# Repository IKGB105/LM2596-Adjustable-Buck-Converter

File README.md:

# Adjustable Buck Converter (LM2596)

Adjustable step-down (buck) power supply based on the LM2596S-ADJ, documented as an honest engineering
logbook: every result is marked as calculated, simulated, or pending — no invented placeholders. A quick,
deliberately simple project in the same series as
[LM317-Adjustable-PowerSupply](https://github.com/IKGB105/LM317-Adjustable-PowerSupply) (same thermal
analysis style, meant as a direct comparison point) — built mainly to get hands-on KiCad PCB layout
experience (placement, trace widths, a ground-plane strategy, via stitching) before moving on to
multiphase VRM work.

- **Input:** 12–40 V DC (datasheet reference design)
- **Adjustable output:** 1.23 V to ≈ 35 V (RV1 position-dependent, see report)
- **Demonstration condition used for thermal comparison:** 12 V → 2 V @ 0.5 A (same load as the LM317
  companion project)

> ⚠️ **Not safe across the full adjustable range.** At the low-output-voltage extreme (35 V → 1.23 V),
> the catch diode D1 exceeds its rated junction temperature above ≈1.5–2 A. This is a genuine finding
> from the COMSOL analysis, documented in Section 7 of the report — not a flaw hidden from this README.

<table>
<tr>
<td><br><sub>KiCad — schematic</sub></td>
<td><br><sub>KiCad — PCB 3D render</sub></td>
<td><br><sub>COMSOL — thermal result (12 V → 2 V, 0.5 A)</sub></td>
</tr>
</table>

## Thermal result (resolved for the demo condition, limitation found at the range's extreme)

- **At 12 V → 2 V, 0.5 A:** COMSOL gives **0.444 W** total estimated loss — **44.3 °C** on the LM2596's
  junction, **52.5 °C** peak on the catch diode (D1). Both comfortably under their rated limits, and a
  large improvement over the LM317 companion project's result at the same load (5.37 W, ≈144 °C with a
  heatsink).
- **Root cause of the D1 limitation above:** a single isolated ground via at D1's anode pad. A fix (more
  copper/vias there) is proposed but **not implemented** in this revision — see the report.

## Repository structure

```
docs/         LaTeX report (lm2596_buck.tex) + figures
LM259/        KiCad project — schematic + PCB, ERC/DRC clean
fem/          COMSOL thermal FEM: exported STEP geometry, result CSVs, figures, model-generation scripts
```

## Document

The full report (reference design, KiCad layout decisions, COMSOL thermal methodology, both operating
points, the D1 root-cause finding, the full modeling/debugging log, limitations) is in
[`docs/lm2596_buck.pdf`](docs/lm2596_buck.pdf) — compiled and committed. Source is
[`docs/lm2596_buck.tex`](docs/lm2596_buck.tex) if you want to edit or recompile it yourself
(`pdflatex`, or [Overleaf](https://www.overleaf.com/)).

## Design (no SPICE simulation — by design)

Topology and component values are taken directly from the LM2596 datasheet's own validated application
circuit (Figure 30, "1.2 to 35 V Adjustable 3.0 A Power Supply"), not re-derived in LTspice — re-simulating
an already-validated manufacturer reference would not have added information, so the time went into the
PCB layout and thermal validation instead, which *are* specific to this board. Full component list and the
output-voltage equation are in the report.

## PCB (KiCad)

In [`LM259/`](LM259/) — ERC and DRC both clean. Two-layer board (not four, unlike the VRM project — a
single ground domain and 3 A don't justify the extra layers). Notable layout decisions, documented in
full in the report:

- Feedback divider (RV1/R1) kept physically separated from L1, following the datasheet's own layout
  app note ("keep feedback wiring away from inductor flux") — deliberately *not* copying a real commercial
  LM2596 module's layout, which places the trimmer right next to the inductor.
- Power traces sized to ≈1.3 mm (IPC-2221, 3 A, conservative 10 °C rise) — correcting an early "as narrow
  as possible" instinct that would have been wrong for the current-carrying nets.
- Bottom-layer solid ground pour, stitched with vias (not via-in-pad, to avoid a solder-wicking risk);
  U1's exposed thermal pad gets 9 vias in a 3×3 grid.

## Thermal FEM (COMSOL)

In [`fem/`](fem/) — *Heat Transfer in Solids*, natural convection, 25 °C ambient, no heatsink. PCB geometry
exported from the KiCad design to STEP; heat sources are **datasheet-derived analytical loss estimates**
(Vsat/Vf scaled from their 3 A datasheet values, assumed 100 ns switching transition) — not measured or
chip-vendor-simulated. Two operating points were solved:

1. **12 V → 2 V, 0.5 A** (demonstration/comparison point) — [`fem/resultados/caso_12V_2V_05A.csv`](fem/resultados/caso_12V_2V_05A.csv)
2. **35 V → 1.23 V, swept 0.5–3 A** (worst case, minimum duty cycle) — [`fem/resultados/barrido_corriente.csv`](fem/resultados/barrido_corriente.csv), with via/radiation/L-loss variants in [`fem/resultados/variantes.csv`](fem/resultados/variantes.csv)

**The worst-case sweep found the catch diode (D1), not the LM2596, is the real thermal limit** — it
exceeds its rated junction temperature above ≈1.5–2 A at this extreme Vin/Vout ratio, even though the
regulator IC itself stays within limits through the full 3 A sweep. See the report for the root-cause
analysis (an isolated ground via at D1's anode) and the proposed, not-yet-implemented fix.

## License

MIT — see [LICENSE](LICENSE).

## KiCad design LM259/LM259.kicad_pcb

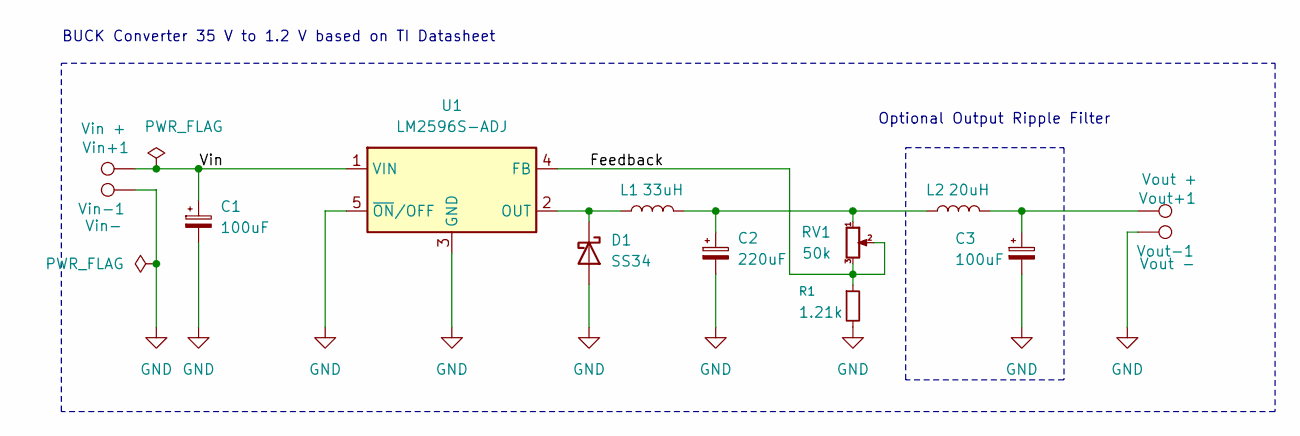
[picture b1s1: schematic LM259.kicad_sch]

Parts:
C1, C3: 100uF; CP_Radial_D8.0mm_P3.50mm
C2: 220uF; CP_Radial_D10.0mm_P5.00mm
D1: SS34; D_SMC
L1: 33uH; L_12x12mm_H4.5mm
L2: 20uH; L_12x12mm_H4.5mm
R1: 1.21k; R_0805_2012Metric_Pad1.20x1.40mm_HandSolder
RV1: 50k; Potentiometer_Bourns_3266Y_Vertical
U1: LM2596S-ADJ; TO-263-5_TabPin3
Vin+1: Vin +; TestPoint_THTPad_3.0x3.0mm_Drill1.5mm
Vin-1: Vin-; TestPoint_THTPad_3.0x3.0mm_Drill1.5mm
Vout+1: Vout +; TestPoint_THTPad_3.0x3.0mm_Drill1.5mm
Vout-1: Vout -; TestPoint_THTPad_3.0x3.0mm_Drill1.5mm

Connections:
/Feedback: R1.1, RV1.2, RV1.3, U1.4 (FB)
/Vin: C1.1, U1.1 (VIN), Vin+1.1 (1_1)
GND: C1.2, C2.2, C3.2, D1.2 (A), R1.2, U1.3 (GND), U1.5 (~ON/OFF), Vin-1.1 (1_1), Vout-1.1 (1_1)
unnamed: C2.1, L1.2, L2.1, RV1.1
unnamed: C3.1, L2.2, Vout+1.1 (1_1)
unnamed: D1.1 (K), L1.1, U1.2 (OUT)

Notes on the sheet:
BUCK Converter 35 V to 1.2 V based on TI Datasheet
Optional Output Ripple Filter

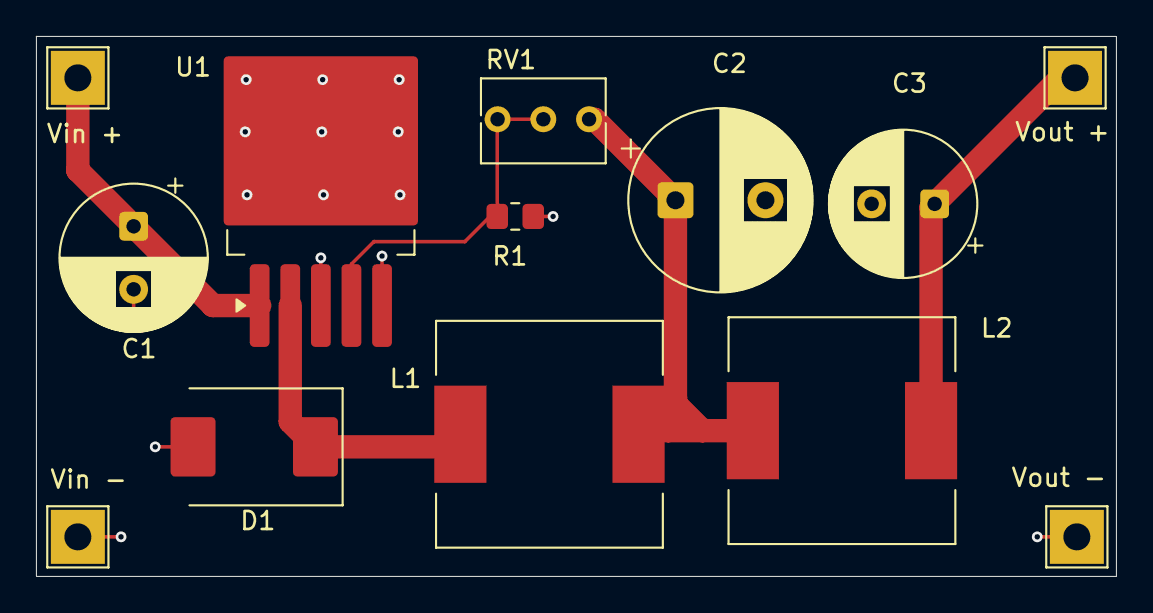
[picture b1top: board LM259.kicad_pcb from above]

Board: 2 copper layers, 60.0 x 30.0 mm, 13 parts (0 on the bottom side), 6 nets.
